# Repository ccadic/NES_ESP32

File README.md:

# NES_ESP32
Nintendo Emulator PCB for ESP32 TTGO

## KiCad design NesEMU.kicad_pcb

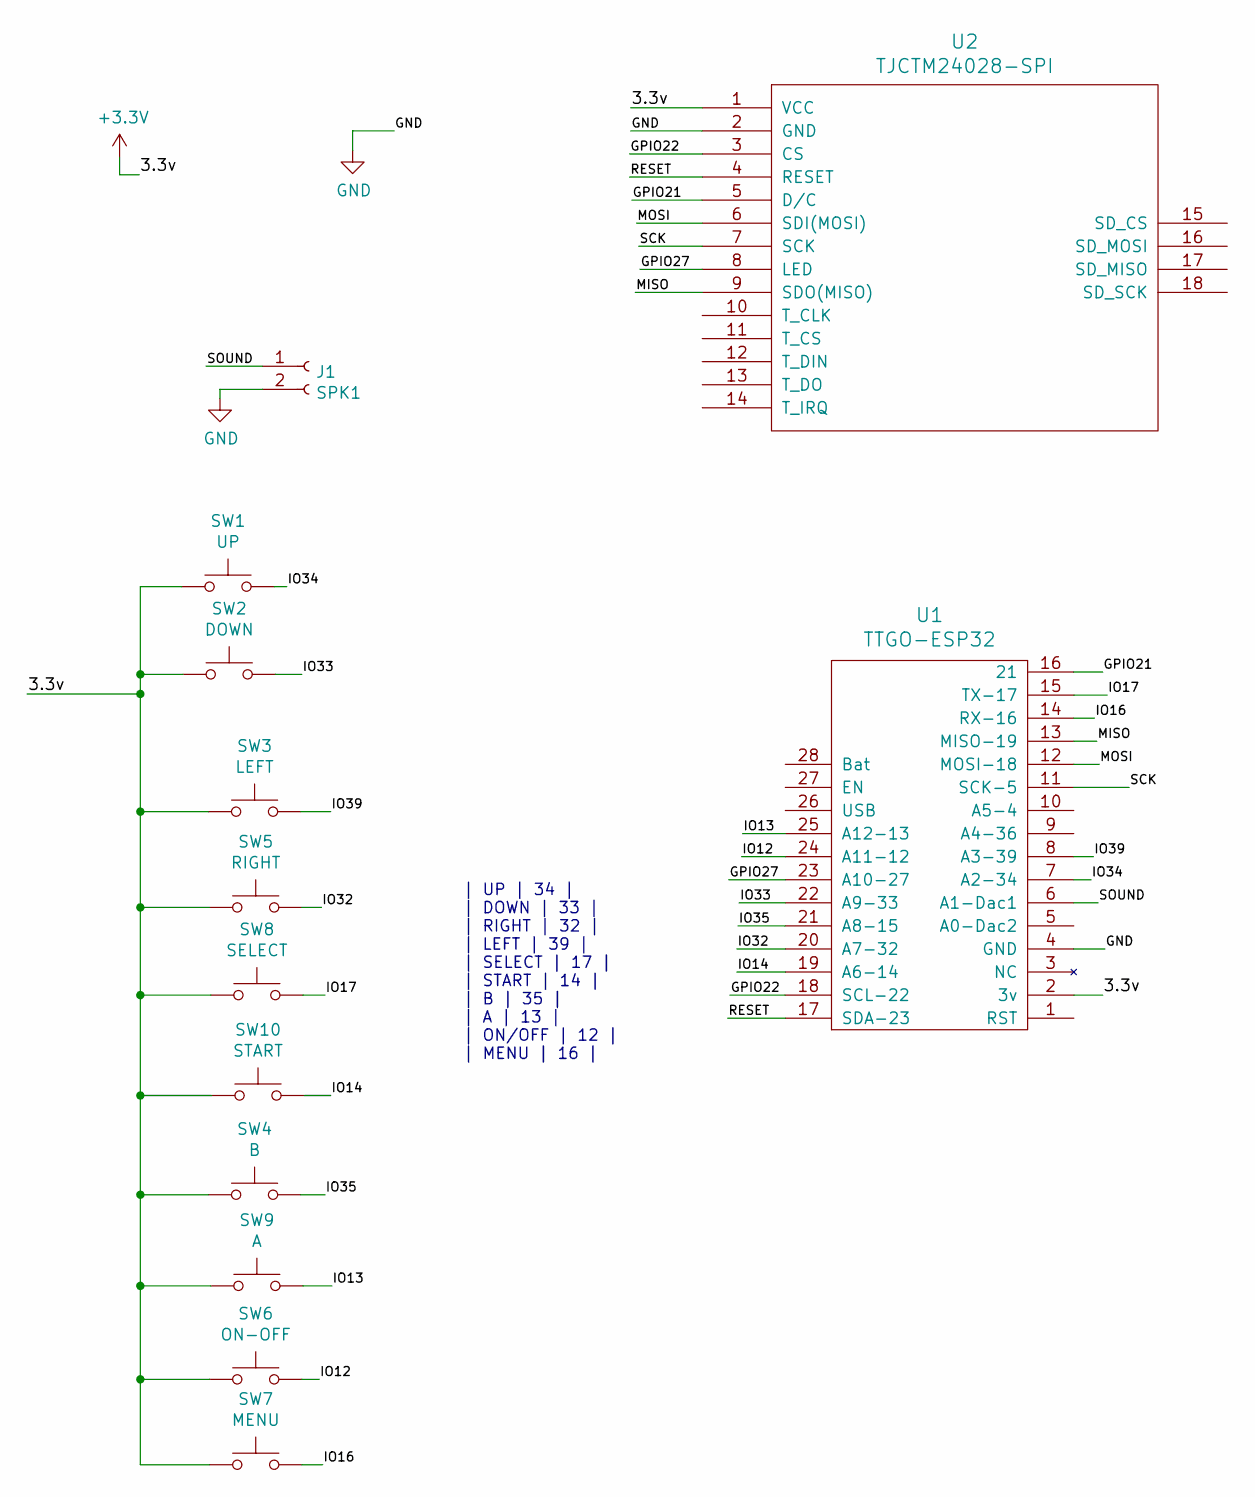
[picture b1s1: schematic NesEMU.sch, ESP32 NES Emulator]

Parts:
J1: SPK1; Socket_Strip_Straight_1x02_Pitch2.54mm
SW1: UP; SW_SPST_B3S-1000
SW2: DOWN; SW_SPST_B3S-1000
SW3: LEFT; SW_SPST_B3S-1000
SW4: B; SW_SPST_B3S-1000
SW5: RIGHT; SW_SPST_B3S-1000
SW6: ON-OFF; SW_SPST_B3S-1000
SW7: MENU; SW_SPST_B3S-1000
SW8: SELECT; SW_SPST_B3S-1000
SW9: A; SW_SPST_B3S-1000
SW10: START; SW_SPST_B3S-1000
U1: TTGO-ESP32
U2: TJCTM24028-SPI

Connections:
+3V3: SW1.1, SW2.1, SW3.1, SW4.1, SW5.1, SW6.1, SW7.1, SW8.1, SW9.1, SW10.1, U1.2 (3v), U2.1 (VCC)
/GPIO21: U1.16 (21), U2.5 (D/C)
/GPIO22: U1.18 (SCL-22), U2.3 (CS)
/GPIO27: U1.23 (A10-27), U2.8 (LED)
/IO12: SW6.2, U1.24 (A11-12)
/IO13: SW9.2, U1.25 (A12-13)
/IO14: SW10.2, U1.19 (A6-14)
/IO16: SW7.2, U1.14 (RX-16)
/IO17: SW8.2, U1.15 (TX-17)
/IO32: SW5.2, U1.20 (A7-32)
/IO33: SW2.2, U1.22 (A9-33)
/IO34: SW1.2, U1.7 (A2-34)
/IO35: SW4.2, U1.21 (A8-15)
/IO39: SW3.2, U1.8 (A3-39)
/MISO: U1.13 (MISO-19), U2.9 (SDO(MISO))
/MOSI: U1.12 (MOSI-18), U2.6 (SDI(MOSI))
/RESET: U1.17 (SDA-23), U2.4 (RESET)
/SCK: U1.11 (SCK-5), U2.7 (SCK)
/SOUND: J1.1, U1.6 (A1-Dac1)
GND: J1.2, U1.4 (GND), U2.2 (GND)

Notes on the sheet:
| UP | 34 | | DOWN | 33 | | RIGHT | 32 | | LEFT | 39 | | SELECT | 17 | | START | 14 | | B | 35 | | A | 13 | | ON/OFF | 12 | | MENU | 16 |

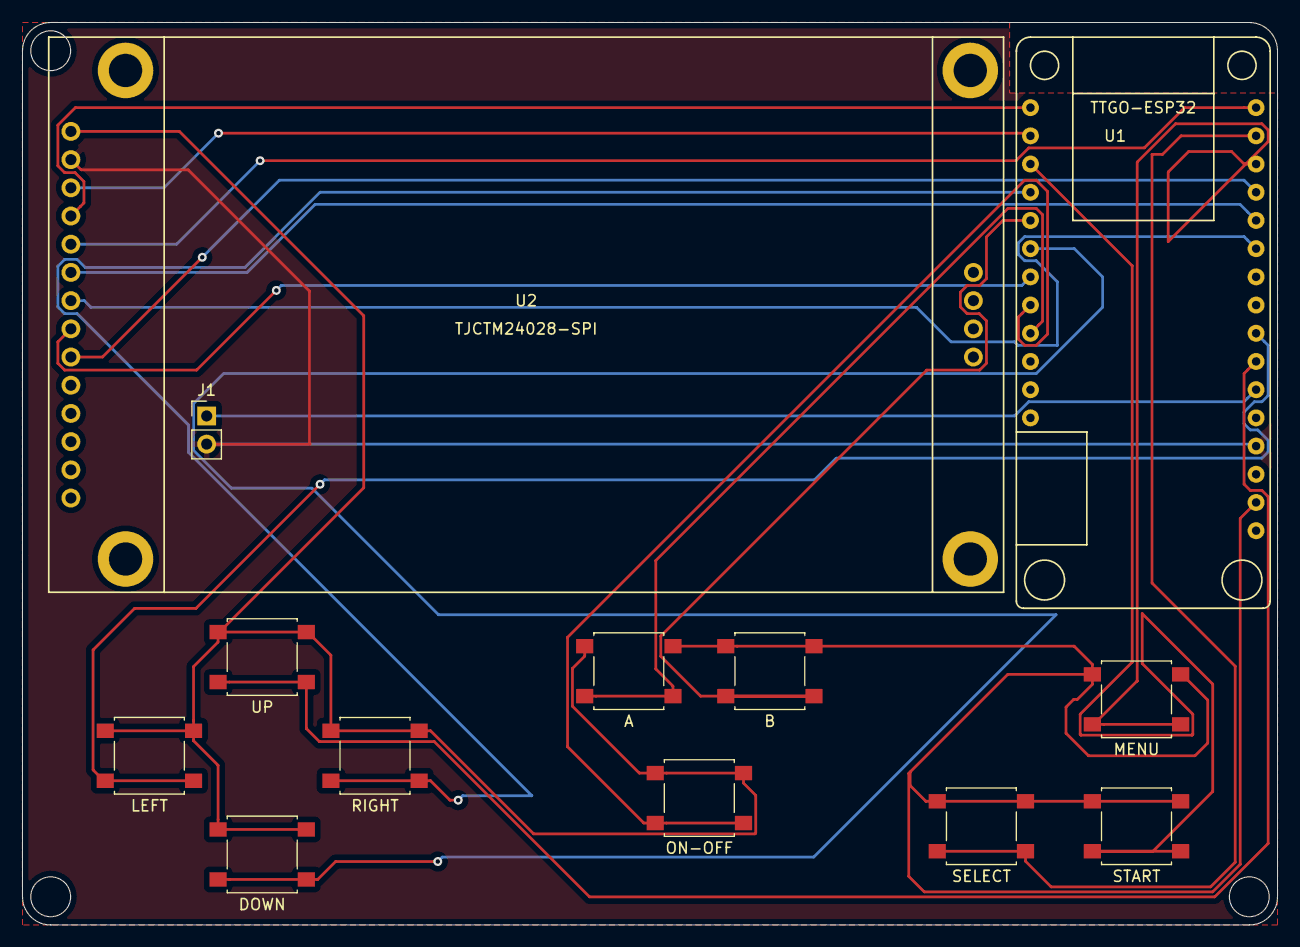
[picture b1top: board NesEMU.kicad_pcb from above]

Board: 2 copper layers, 113.0 x 81.3 mm, 13 parts (0 on the bottom side), 20 nets.
